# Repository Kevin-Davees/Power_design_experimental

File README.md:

# Experimental 20A Battery Charger PCB (Failed Design)

## Overview

This repository contains an early experimental PCB design for a 20A battery charger with an integrated battery protection IC.

This design is one of my early PCB layout attempts and is NOT suitable for manufacturing, production, or real-world usage.

The design is published only for documentation and learning purposes.

IMPORTANT:
This design contains major electrical and thermal design flaws.

DO NOT attempt to manufacture, assemble, or use this PCB in any real system.

---

## Project Intent

The purpose of publishing this repository is to:

- Document early design mistakes
- Demonstrate poor high-current PCB layout practices
- Help others understand what not to do in power PCB design
- Track personal learning progress in PCB development

---

## Major Design Problems

This PCB has multiple serious issues that make it unsuitable for high-current applications.

### 1. Poor Copper Pour Design

The copper pour implementation is incorrect and does not properly support high current flow.

Problems include:

- Poor copper distribution
- Narrow current paths for a 20A design
- Inconsistent copper connectivity
- Inefficient current return paths
- Copper pours that do not significantly reduce resistance

A 20A power design requires much larger copper areas and carefully designed current paths.

---

### 2. Bad Heat Dissipation

Thermal management in this PCB is insufficient.

Issues include:

- High-current components lacking adequate copper area for heat spreading
- No effective thermal vias
- Poor thermal distribution across the board
- Suboptimal placement of power components

Under high load, this design would likely overheat.

---

### 3. Layout Not Suitable for High Current

The PCB layout does not follow correct high-current design practices.

Examples:

- Trace widths are insufficient for a 20A system
- Power routing is inefficient
- High-current paths are not optimized
- Potential voltage drop across traces

A properly designed 20A charger PCB requires extremely low resistance power paths, which this design does not provide.

---

### 4. Experimental Quality Layout

This board was created while learning PCB design fundamentals.

As a result:

- The layout structure is not professional
- Power routing is poorly optimized
- Thermal considerations are inadequate
- Design rule practices are incomplete

---

---

---

---

---

## Warning

This PCB should NOT be used for:

- Manufacturing
- Commercial products
- Battery charging systems
- High current electronics
- Safety critical applications

Using this design may result in:

- Overheating
- PCB damage
- Component failure
- Safety hazards

---

## Why This Repository Exists

Engineering improvement comes from learning through mistakes.

This repository exists to:

- Document an early failed design
- Maintain a record of design evolution
- Show progress in PCB design skills over time

Future designs will focus on:

- Proper high-current layout techniques
- Correct copper pour usage
- Improved thermal management
- Better power routing practices

---

## License

Shared for educational and documentation purposes only.

Use the files at your own risk.

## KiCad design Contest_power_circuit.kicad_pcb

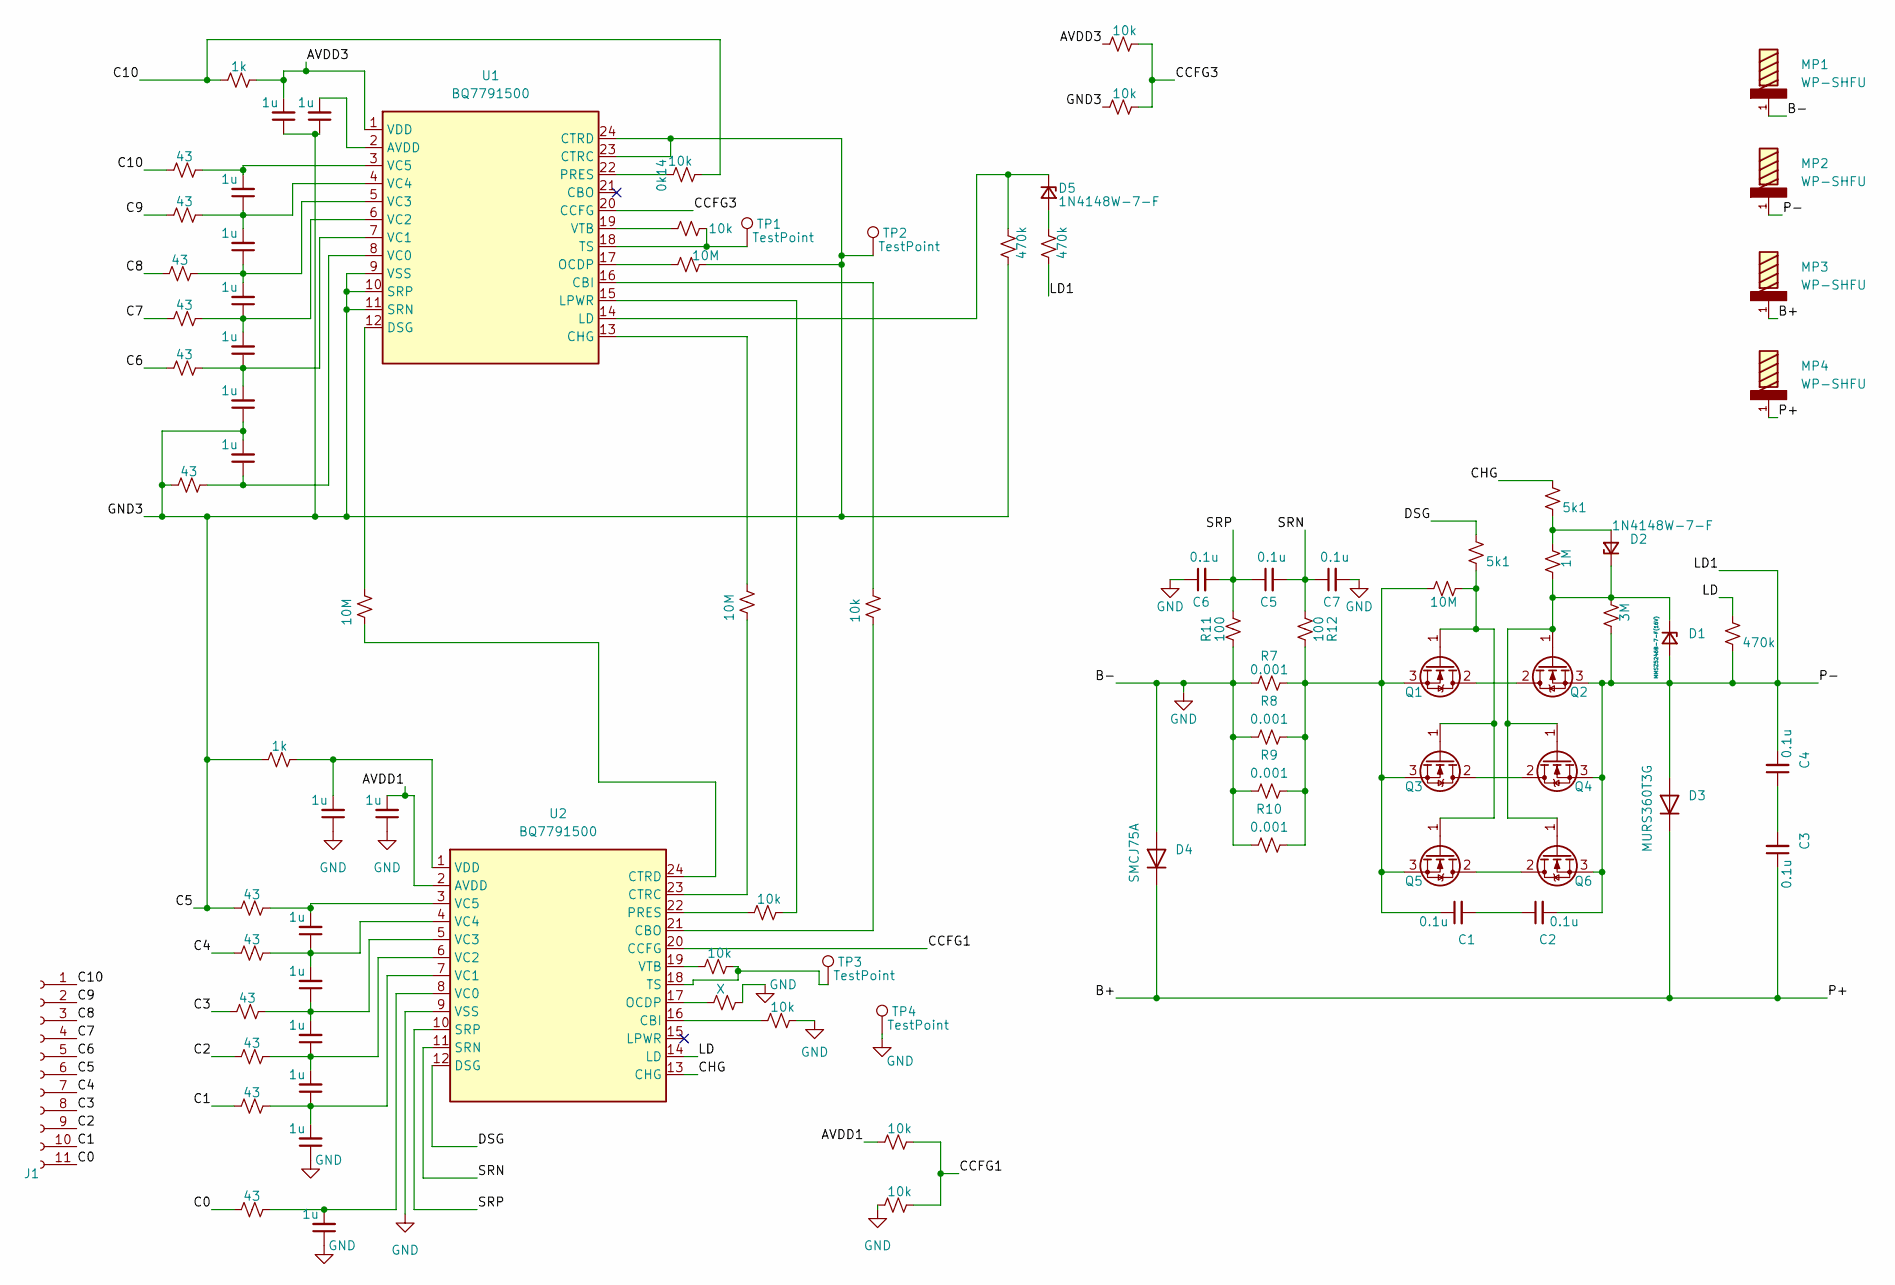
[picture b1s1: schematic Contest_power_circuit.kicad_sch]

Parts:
0k1, 0k3, 0k6, 0k7, 0k9, 0k10, 0k11, 0k12, 0k13, 0k14: 10k; R_0805_2012Metric
0k2, 0k4, 0k5: 10M; R_0805_2012Metric
0k8: X; R_0805_2012Metric
C1, C2, C3, C4, C5, C6, C7: 0.1u; C_0603_1608Metric
C8, C9, C10, C11, C12, C13, C14, C15, C16, C17, C18, C19, C20, C21, C22, C23: 1u; C_0805_2012Metric
D1: MMSZ5246B-7-F(16V); D_SOD-123
D2, D5: 1N4148W-7-F; D_SOD-123
D3: MURS360T3G; D_SMC
D4: SMCJ75A; D_SMC
J1: Conn_01x11_Socket; PinHeader_1x11_P2.54mm_Vertical
MP1, MP2, MP3, MP4: WP-SHFU; WP-SHFU_7461096
Q1, Q2, Q3, Q4, Q5, Q6: AOB290L; TO-263-2
R1: 10M; R_0805_2012Metric
R2, R4: 5k1; R_0805_2012Metric
R3: 1M; R_0805_2012Metric
R5: 3M; R_0805_2012Metric
R6, R20, R21: 470k; R_1206_3216Metric
R7, R8, R9, R10: 0.001; R_2512_6332Metric
R11, R12: 100; R_0805_2012Metric
R13, R28: 1k; R_0805_2012Metric
R14, R15, R16, R17, R18, R19, R22, R23, R24, R25, R26, R27: 43; R_1206_3216Metric
TP1, TP2, TP3, TP4: TestPoint; TestPoint_Pad_D2.5mm
U1, U2: BQ7791500; TSSOP-24_4.4x7.8mm_P0.65mm

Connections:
/AVDD1: 0k10.2, C23.2, U2.2 (AVDD)
/AVDD3: 0k12.2, C8.2, R13.2, U1.1 (VDD)
/B+: C3.1, D3.1 (K), D4.1 (K), MP3.1, MP3.2, MP3.3, MP3.4, MP3.5, MP3.6, MP3.7, MP3.8, MP3.9, MP4.1, MP4.2, MP4.3, MP4.4, MP4.5, MP4.6, MP4.7, MP4.8, MP4.9
/C0: J1.11, R27.1
/C1: J1.10, R26.1
/C2: J1.9, R25.1
/C3: J1.8, R22.1
/C4: J1.7, R24.1
/C5: 0k2.2, 0k13.2, C8.1, C9.1, C14.1, C15.2, J1.6, R19.1, R21.2, R23.1, R28.1, TP2.1, U1.9 (VSS), U1.10 (SRP), U1.11 (SRN), U1.23 (CTRC), U1.24 (CTRD)
/C6: J1.5, R18.1
/C7: J1.4, R17.1
/C8: J1.3, R16.1
/C9: J1.2, R15.1
/C10: 0k14.2, J1.1, R13.1, R14.1
/CCFG1: 0k10.1, 0k11.1, U2.20 (CCFG)
/CCFG3: 0k12.1, 0k13.1, U1.20 (CCFG)
/CHG: R4.1, U2.13 (CHG)
/DSG: R2.1, U2.12 (DSG)
/LD: R6.1, U2.14 (LD)
/LD1: C2.2, C4.2, D1.2 (A), D3.2 (A), MP2.1, MP2.2, MP2.3, MP2.4, MP2.5, MP2.6, MP2.7, MP2.8, MP2.9, Q2.3 (S), Q4.3 (S), Q6.3 (S), R5.1, R6.2, R20.2
/SRN: C5.2, C7.1, R12.1, U2.11 (SRN)
/SRP: C5.1, C6.2, R11.2, U2.10 (SRP)
GND: 0k7.1, 0k8.1, 0k11.2, C6.1, C7.2, C20.1, C21.1, C22.1, C23.1, D4.2 (A), MP1.1, MP1.2, MP1.3, MP1.4, MP1.5, MP1.6, MP1.7, MP1.8, MP1.9, R7.1, R8.1, R9.1, R10.1, R11.1, TP4.1, U2.9 (VSS)
unnamed: C1.2, C2.1
unnamed: C3.2, C4.1
unnamed: D1.1 (K), D2.1 (K), Q2.1 (G), Q4.1 (G), Q6.1 (G), R3.1, R5.2
unnamed: D2.2 (A), R3.2, R4.2
unnamed: D5.2 (A), R20.1
unnamed: D5.1 (K), R21.1, U1.14 (LD)
unnamed: Q1.2 (D), Q2.2 (D)
unnamed: Q1.1 (G), Q3.1 (G), Q5.1 (G), R1.2, R2.2
unnamed: C1.1, Q1.3 (S), Q3.3 (S), Q5.3 (S), R1.1, R7.2, R8.2, R9.2, R10.2, R12.2
unnamed: Q3.2 (D), Q4.2 (D)
unnamed: Q5.2 (D), Q6.2 (D)
unnamed: C9.2, U1.2 (AVDD)
unnamed: 0k3.2, U1.16 (CBI)
unnamed: 0k4.2, U1.13 (CHG)
unnamed: 0k5.2, U1.12 (DSG)
unnamed: 0k6.1, U1.15 (LPWR)
unnamed: 0k2.1, U1.17 (OCDP)
unnamed: 0k14.1, U1.22 (PRES)
unnamed: 0k1.2, TP1.1, U1.18 (TS)
unnamed: C15.1, R19.2, U1.8 (VC0)
unnamed: C13.1, C14.2, R18.2, U1.7 (VC1)
unnamed: C12.1, C13.2, R17.2, U1.6 (VC2)
unnamed: C11.1, C12.2, R16.2, U1.5 (VC3)
unnamed: C10.1, C11.2, R15.2, U1.4 (VC4)
unnamed: C10.2, R14.2, U1.3 (VC5)
unnamed: 0k1.1, U1.19 (VTB)
unnamed: 0k7.2, U2.16 (CBI)
unnamed: 0k3.1, U2.21 (CBO)
unnamed: 0k4.1, U2.23 (CTRC)
unnamed: 0k5.1, U2.24 (CTRD)
unnamed: 0k8.2, U2.17 (OCDP)
unnamed: 0k6.2, U2.22 (PRES)
unnamed: 0k9.1, TP3.1, U2.18 (TS)
unnamed: C21.2, R27.2, U2.8 (VC0)
unnamed: C19.1, C20.2, R26.2, U2.7 (VC1)
unnamed: C18.1, C19.2, R25.2, U2.6 (VC2)
unnamed: C17.1, C18.2, R22.2, U2.5 (VC3)
unnamed: C16.1, C17.2, R24.2, U2.4 (VC4)
unnamed: C16.2, R23.2, U2.3 (VC5)
unnamed: C22.2, R28.2, U2.1 (VDD)
unnamed: 0k9.2, U2.19 (VTB)

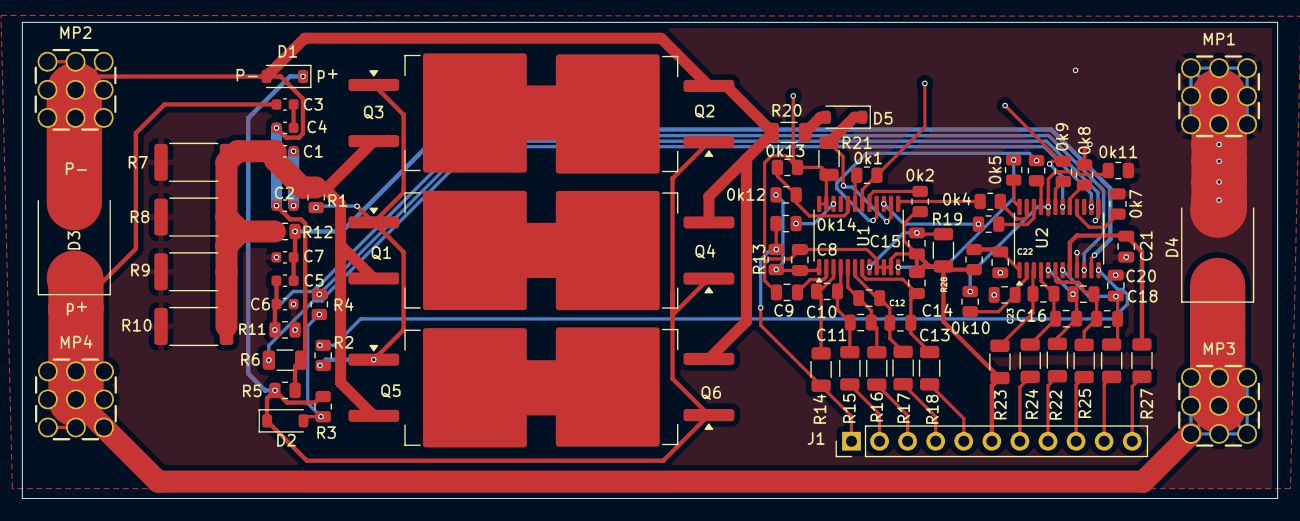
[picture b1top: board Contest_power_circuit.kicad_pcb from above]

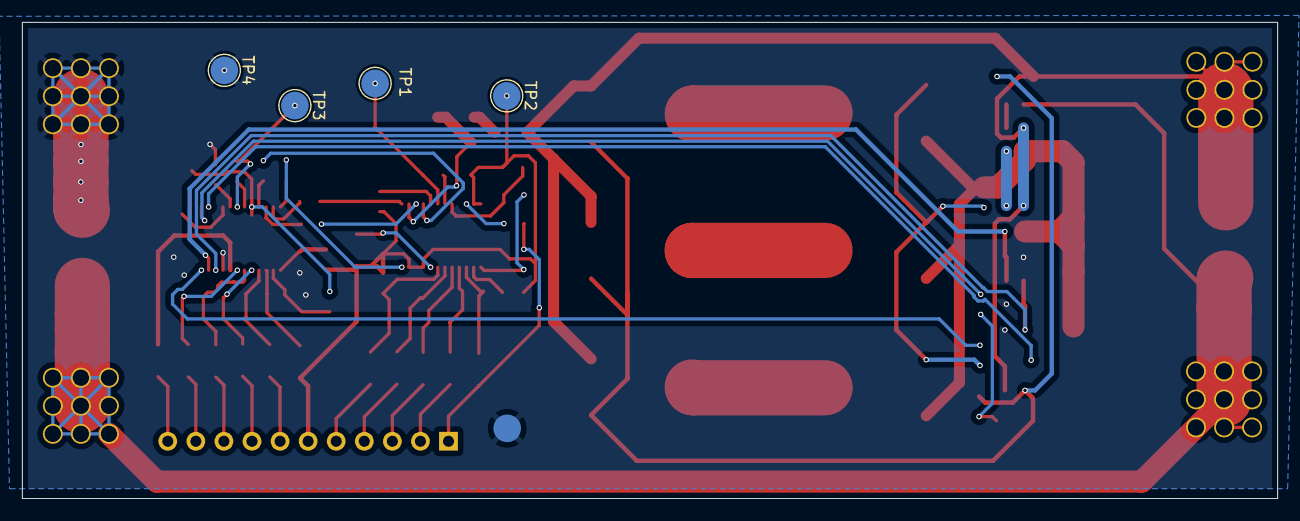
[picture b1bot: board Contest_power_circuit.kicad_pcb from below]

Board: 2 copper layers, 113.6 x 43.1 mm, 87 parts (4 on the bottom side), 64 nets.

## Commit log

2026-03-31 Create assets
2026-03-31 Create main
